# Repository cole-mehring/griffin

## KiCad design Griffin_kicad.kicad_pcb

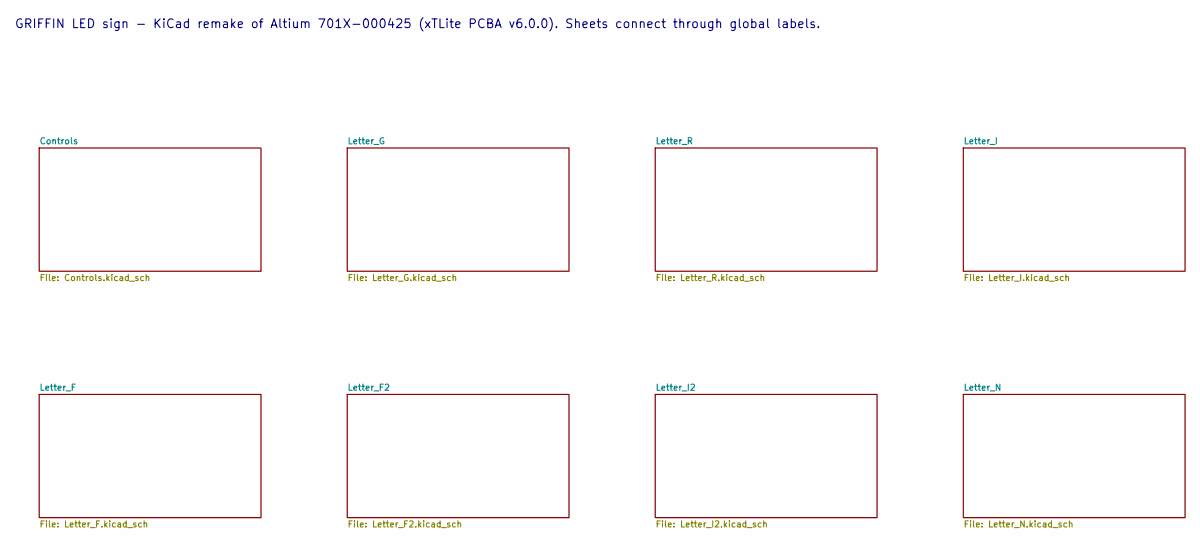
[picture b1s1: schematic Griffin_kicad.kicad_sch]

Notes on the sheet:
GRIFFIN LED sign - KiCad remake of Altium 701X-000425 (xTLite PCBA v6.0.0). Sheets connect through global labels.

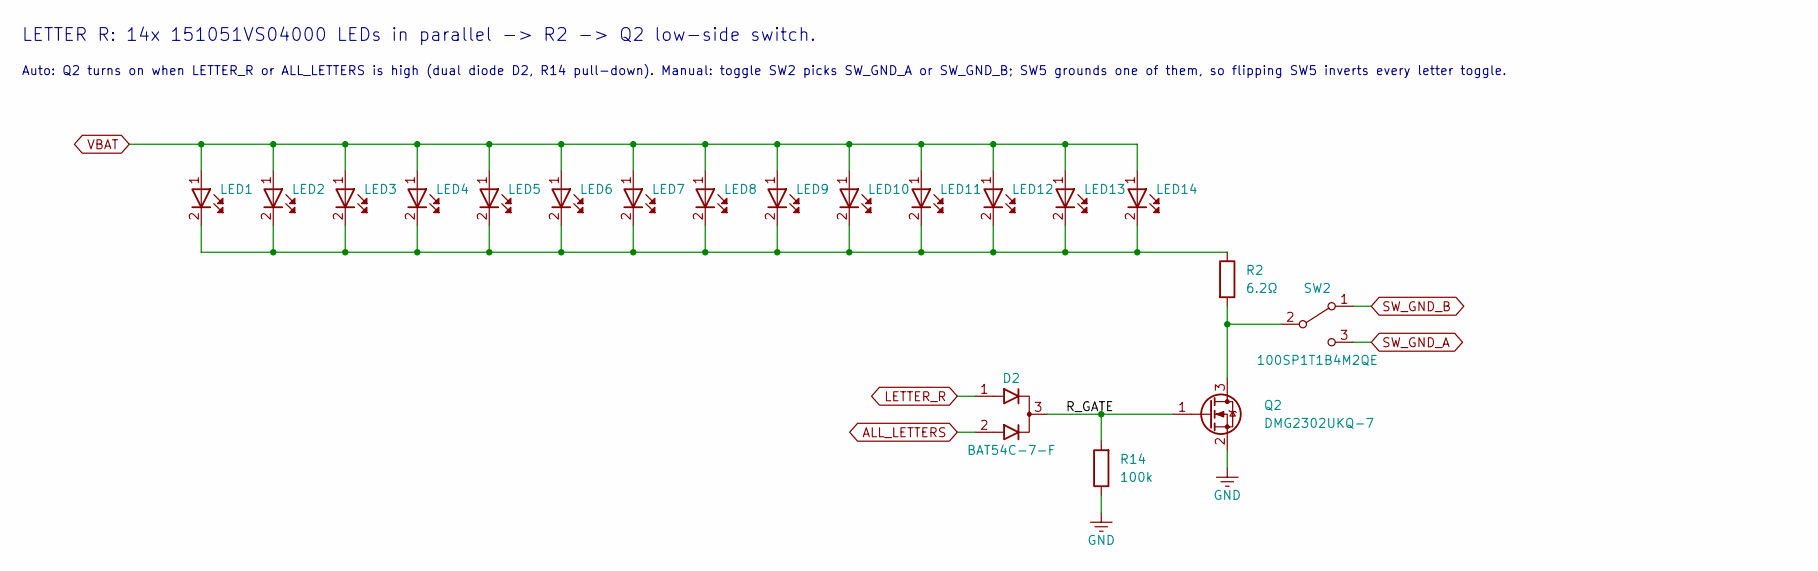
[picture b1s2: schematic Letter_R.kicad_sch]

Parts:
D2: BAT54C-7-F; SOT-23_Diodes; MPN BAT54C-7-F
LED1, LED2, LED3, LED4, LED5, LED6, LED7, LED8, LED9, LED10, LED11, LED12, LED13, LED14: 151051VS04000; LED_D5.0mm_WE-WL-TMRC_AnodePin1; MPN 151051VS04000
Q2: DMG2302UKQ-7; SOT-23_Diodes; MPN DMG2302UKQ-7
R2: 6.2Ω; R_1206_3216Metric; MPN RC1206FR-076R2L
R14: 100k; R_0805_2012Metric; MPN RC0805FR-07100KL
SW2: 100SP1T1B4M2QE; SW_Toggle_E-Switch_100SP_M2_P4.70mm; MPN 100SP1T1B4M2QE

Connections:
/Letter_R/R_GATE: D2.3 (K), Q2.1 (G), R14.2
ALL_LETTERS: D2.2 (A2); also elsewhere on the board
GND: Q2.2 (S), R14.1; also elsewhere on the board
LETTER_R: D2.1 (A1); also elsewhere on the board
unnamed: LED1.2 (K), LED2.2 (K), LED3.2 (K), LED4.2 (K), LED5.2 (K), LED6.2 (K), LED7.2 (K), LED8.2 (K), LED9.2 (K), LED10.2 (K), LED11.2 (K), LED12.2 (K), LED13.2 (K), LED14.2 (K), R2.1
unnamed: Q2.3 (D), R2.2, SW2.2 (C)
SW_GND_A: SW2.3 (B); also elsewhere on the board
SW_GND_B: SW2.1 (A); also elsewhere on the board
VBAT: LED1.1 (A), LED2.1 (A), LED3.1 (A), LED4.1 (A), LED5.1 (A), LED6.1 (A), LED7.1 (A), LED8.1 (A), LED9.1 (A), LED10.1 (A), LED11.1 (A), LED12.1 (A), LED13.1 (A), LED14.1 (A); also elsewhere on the board

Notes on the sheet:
Auto: Q2 turns on when LETTER_R or ALL_LETTERS is high (dual diode D2, R14 pull-down). Manual: toggle SW2 picks SW_GND_A or SW_GND_B; SW5 grounds one of them, so flipping SW5 inverts every letter toggle.
LETTER R: 14x 151051VS04000 LEDs in parallel -> R2 -> Q2 low-side switch.

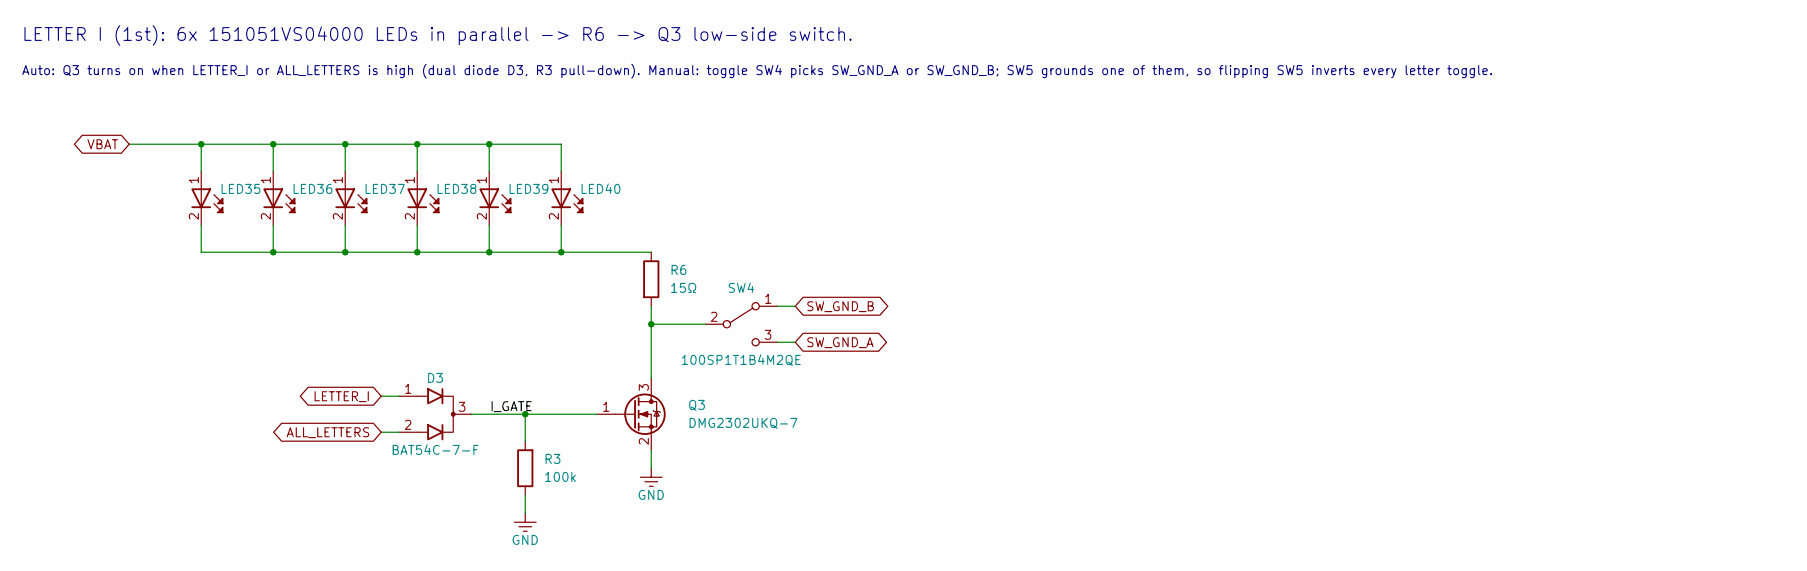
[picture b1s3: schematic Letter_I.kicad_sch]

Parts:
D3: BAT54C-7-F; SOT-23_Diodes; MPN BAT54C-7-F
LED35, LED36, LED37, LED38, LED39, LED40: 151051VS04000; LED_D5.0mm_WE-WL-TMRC_AnodePin1; MPN 151051VS04000
Q3: DMG2302UKQ-7; SOT-23_Diodes; MPN DMG2302UKQ-7
R3: 100k; R_0805_2012Metric; MPN RC0805FR-07100KL
R6: 15Ω; R_1206_3216Metric; MPN RC1206FR-0715RL
SW4: 100SP1T1B4M2QE; SW_Toggle_E-Switch_100SP_M2_P4.70mm; MPN 100SP1T1B4M2QE

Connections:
/Letter_I/I_GATE: D3.3 (K), Q3.1 (G), R3.2
ALL_LETTERS: D3.2 (A2); also elsewhere on the board
GND: Q3.2 (S), R3.1; also elsewhere on the board
LETTER_I: D3.1 (A1); also elsewhere on the board
unnamed: LED35.2 (K), LED36.2 (K), LED37.2 (K), LED38.2 (K), LED39.2 (K), LED40.2 (K), R6.1
unnamed: Q3.3 (D), R6.2, SW4.2 (C)
SW_GND_A: SW4.3 (B); also elsewhere on the board
SW_GND_B: SW4.1 (A); also elsewhere on the board
VBAT: LED35.1 (A), LED36.1 (A), LED37.1 (A), LED38.1 (A), LED39.1 (A), LED40.1 (A); also elsewhere on the board

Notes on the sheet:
Auto: Q3 turns on when LETTER_I or ALL_LETTERS is high (dual diode D3, R3 pull-down). Manual: toggle SW4 picks SW_GND_A or SW_GND_B; SW5 grounds one of them, so flipping SW5 inverts every letter toggle.
LETTER I (1st): 6x 151051VS04000 LEDs in parallel -> R6 -> Q3 low-side switch.

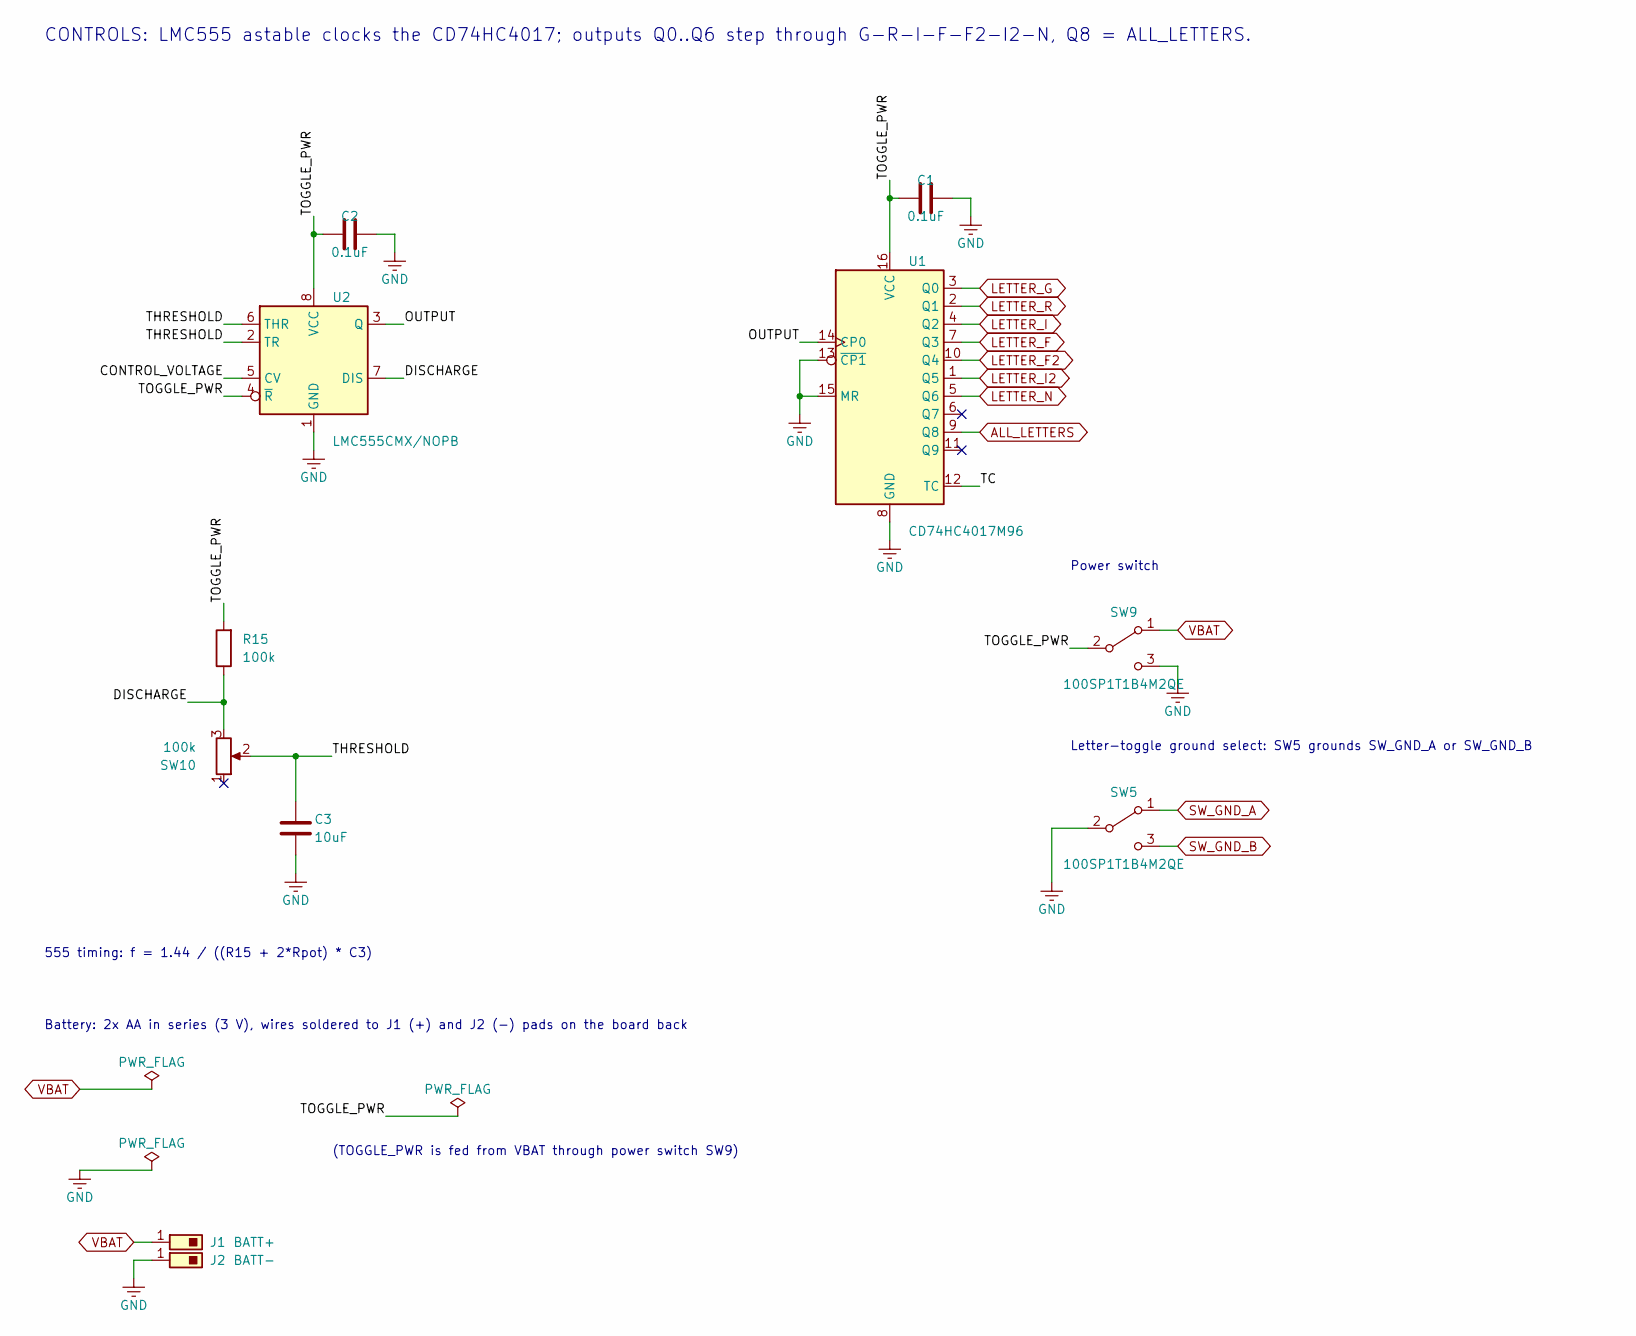
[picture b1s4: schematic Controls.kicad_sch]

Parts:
C1, C2: 0.1uF; C_0805_2012Metric; MPN CC0805KRX7R9BB104
C3: 10uF; C_0805_2012Metric; MPN GRM21BR61E106KA73L
J1: BATT+; SolderPad_1x1_8x8mm
J2: BATT-; SolderPad_1x1_8x8mm
R15: 100k; R_0805_2012Metric; MPN RC0805FR-07100KL
SW5, SW9: 100SP1T1B4M2QE; SW_Toggle_E-Switch_100SP_M2_P4.70mm; MPN 100SP1T1B4M2QE
SW10: 100k; Potentiometer_Bourns_PTV09A-4_Single_Vertical; MPN PTV09A-4025F-B104
U1: CD74HC4017M96; SOIC-16_3.9x9.9mm_P1.27mm; MPN CD74HC4017M96
U2: LMC555CMX/NOPB; SOIC-8_3.9x4.9mm_P1.27mm; MPN LMC555CMX/NOPB

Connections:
/Controls/CONTROL_VOLTAGE: U2.5 (CV)
/Controls/DISCHARGE: R15.1, SW10.3, U2.7 (DIS)
/Controls/OUTPUT: U1.14 (CP0), U2.3 (Q)
/Controls/TC: U1.12 (TC)
/Controls/THRESHOLD: C3.1, SW10.2, U2.2 (TR), U2.6 (THR)
/Controls/TOGGLE_PWR: C1.1, C2.1, R15.2, SW9.2 (C), U1.16 (VCC), U2.4 (~R), U2.8 (VCC)
ALL_LETTERS: U1.9 (Q8); also elsewhere on the board
GND: C1.2, C2.2, C3.2, J2.1 (~_1), SW5.2 (C), SW9.3 (B), U1.8 (GND), U1.13 (~CP1), U1.15 (MR), U2.1 (GND); also elsewhere on the board
LETTER_F: U1.7 (Q3); also elsewhere on the board
LETTER_F2: U1.10 (Q4); also elsewhere on the board
LETTER_G: U1.3 (Q0); also elsewhere on the board
LETTER_I: U1.4 (Q2); also elsewhere on the board
LETTER_I2: U1.1 (Q5); also elsewhere on the board
LETTER_N: U1.5 (Q6); also elsewhere on the board
LETTER_R: U1.2 (Q1); also elsewhere on the board
SW_GND_A: SW5.1 (A); also elsewhere on the board
SW_GND_B: SW5.3 (B); also elsewhere on the board
VBAT: J1.1 (~_1), SW9.1 (A); also elsewhere on the board

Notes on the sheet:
(TOGGLE_PWR is fed from VBAT through power switch SW9)
Battery: 2x AA in series (3 V), wires soldered to J1 (+) and J2 (-) pads on the board back
Letter-toggle ground select: SW5 grounds SW_GND_A or SW_GND_B
555 timing: f = 1.44 / ((R15 + 2*Rpot) * C3)
CONTROLS: LMC555 astable clocks the CD74HC4017; outputs Q0..Q6 step through G-R-I-F-F2-I2-N, Q8 = ALL_LETTERS.
Power switch

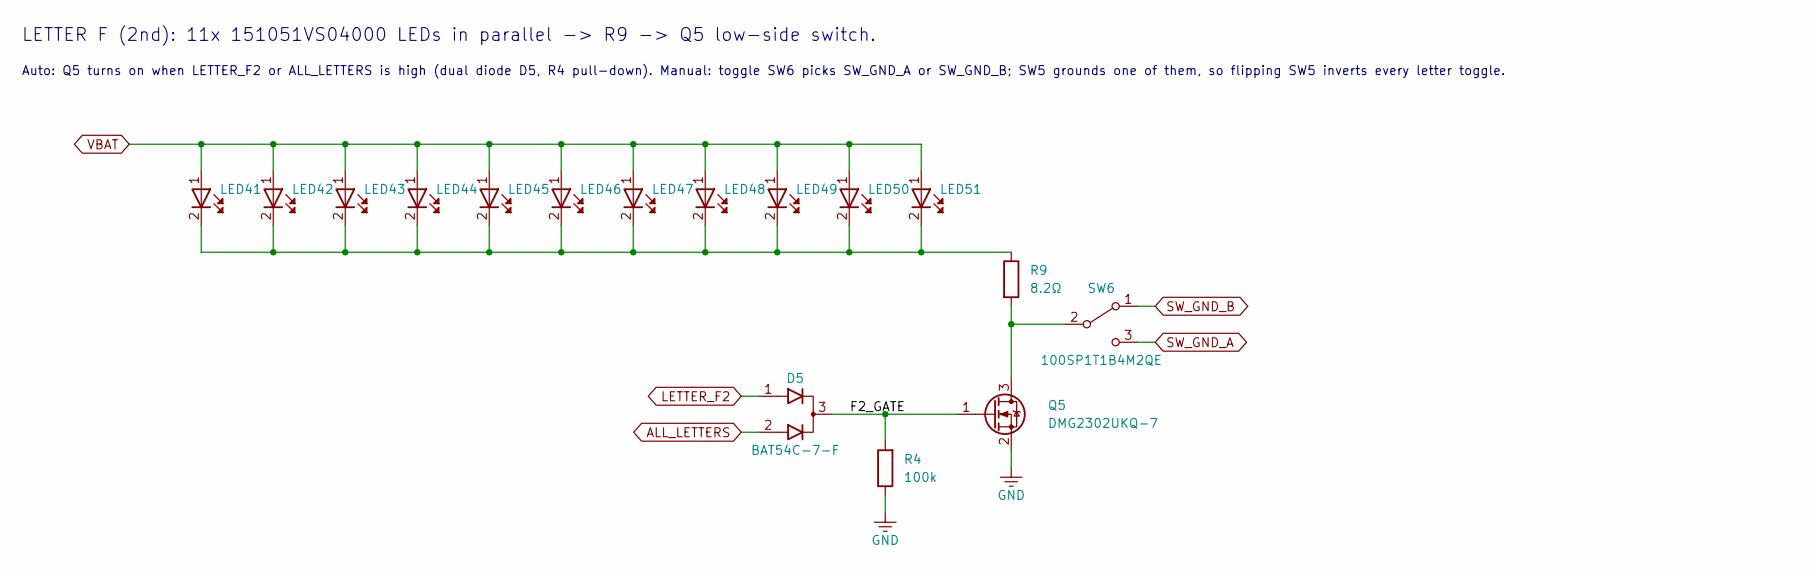
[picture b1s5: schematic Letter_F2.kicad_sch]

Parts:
D5: BAT54C-7-F; SOT-23_Diodes; MPN BAT54C-7-F
LED41, LED42, LED43, LED44, LED45, LED46, LED47, LED48, LED49, LED50, LED51: 151051VS04000; LED_D5.0mm_WE-WL-TMRC_AnodePin1; MPN 151051VS04000
Q5: DMG2302UKQ-7; SOT-23_Diodes; MPN DMG2302UKQ-7
R4: 100k; R_0805_2012Metric; MPN RC0805FR-07100KL
R9: 8.2Ω; R_1206_3216Metric; MPN RC1206FR-078R2L
SW6: 100SP1T1B4M2QE; SW_Toggle_E-Switch_100SP_M2_P4.70mm; MPN 100SP1T1B4M2QE

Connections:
/Letter_F2/F2_GATE: D5.3 (K), Q5.1 (G), R4.2
ALL_LETTERS: D5.2 (A2); also elsewhere on the board
GND: Q5.2 (S), R4.1; also elsewhere on the board
LETTER_F2: D5.1 (A1); also elsewhere on the board
unnamed: LED41.2 (K), LED42.2 (K), LED43.2 (K), LED44.2 (K), LED45.2 (K), LED46.2 (K), LED47.2 (K), LED48.2 (K), LED49.2 (K), LED50.2 (K), LED51.2 (K), R9.1
unnamed: Q5.3 (D), R9.2, SW6.2 (C)
SW_GND_A: SW6.3 (B); also elsewhere on the board
SW_GND_B: SW6.1 (A); also elsewhere on the board
VBAT: LED41.1 (A), LED42.1 (A), LED43.1 (A), LED44.1 (A), LED45.1 (A), LED46.1 (A), LED47.1 (A), LED48.1 (A), LED49.1 (A), LED50.1 (A), LED51.1 (A); also elsewhere on the board

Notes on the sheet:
Auto: Q5 turns on when LETTER_F2 or ALL_LETTERS is high (dual diode D5, R4 pull-down). Manual: toggle SW6 picks SW_GND_A or SW_GND_B; SW5 grounds one of them, so flipping SW5 inverts every letter toggle.
LETTER F (2nd): 11x 151051VS04000 LEDs in parallel -> R9 -> Q5 low-side switch.

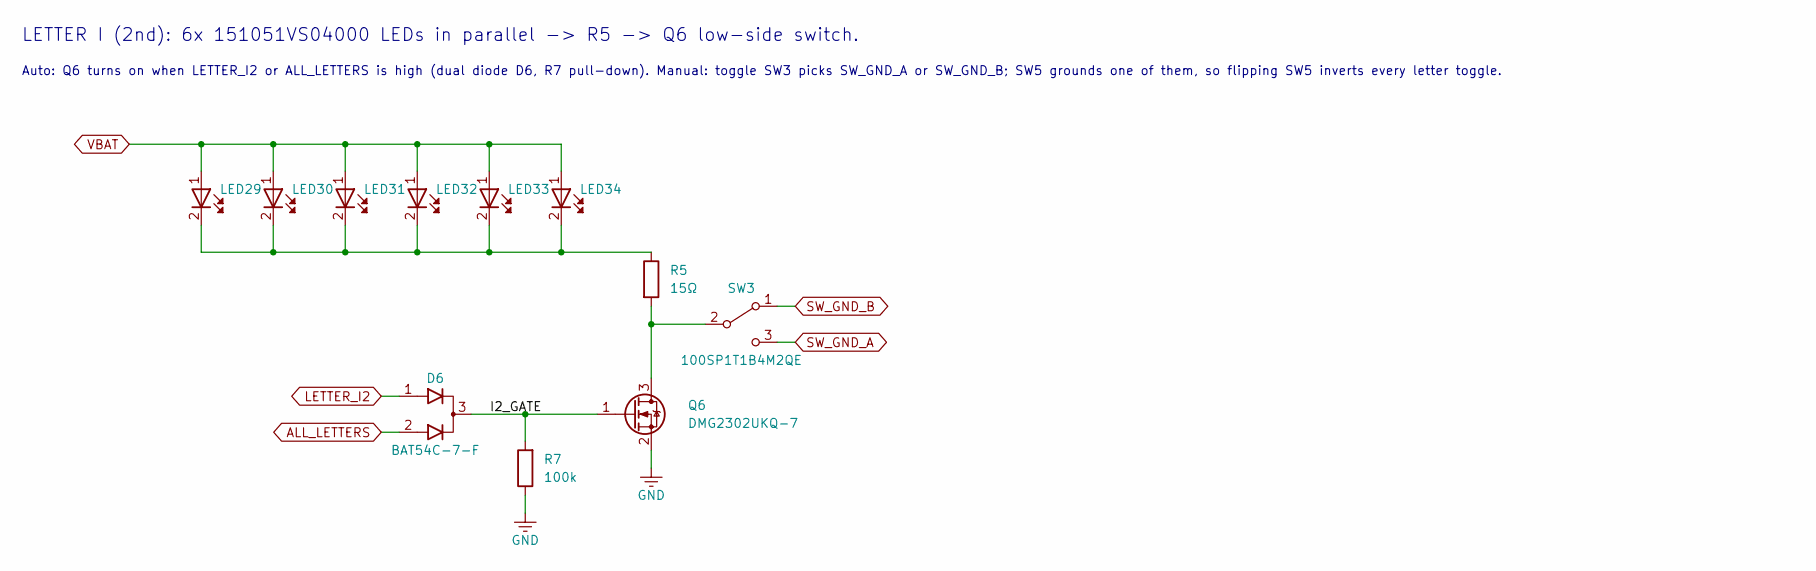
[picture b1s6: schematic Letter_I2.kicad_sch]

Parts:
D6: BAT54C-7-F; SOT-23_Diodes; MPN BAT54C-7-F
LED29, LED30, LED31, LED32, LED33, LED34: 151051VS04000; LED_D5.0mm_WE-WL-TMRC_AnodePin1; MPN 151051VS04000
Q6: DMG2302UKQ-7; SOT-23_Diodes; MPN DMG2302UKQ-7
R5: 15Ω; R_1206_3216Metric; MPN RC1206FR-0715RL
R7: 100k; R_0805_2012Metric; MPN RC0805FR-07100KL
SW3: 100SP1T1B4M2QE; SW_Toggle_E-Switch_100SP_M2_P4.70mm; MPN 100SP1T1B4M2QE

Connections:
/Letter_I2/I2_GATE: D6.3 (K), Q6.1 (G), R7.2
ALL_LETTERS: D6.2 (A2); also elsewhere on the board
GND: Q6.2 (S), R7.1; also elsewhere on the board
LETTER_I2: D6.1 (A1); also elsewhere on the board
unnamed: LED29.2 (K), LED30.2 (K), LED31.2 (K), LED32.2 (K), LED33.2 (K), LED34.2 (K), R5.1
unnamed: Q6.3 (D), R5.2, SW3.2 (C)
SW_GND_A: SW3.3 (B); also elsewhere on the board
SW_GND_B: SW3.1 (A); also elsewhere on the board
VBAT: LED29.1 (A), LED30.1 (A), LED31.1 (A), LED32.1 (A), LED33.1 (A), LED34.1 (A); also elsewhere on the board

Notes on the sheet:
LETTER I (2nd): 6x 151051VS04000 LEDs in parallel -> R5 -> Q6 low-side switch.
Auto: Q6 turns on when LETTER_I2 or ALL_LETTERS is high (dual diode D6, R7 pull-down). Manual: toggle SW3 picks SW_GND_A or SW_GND_B; SW5 grounds one of them, so flipping SW5 inverts every letter toggle.

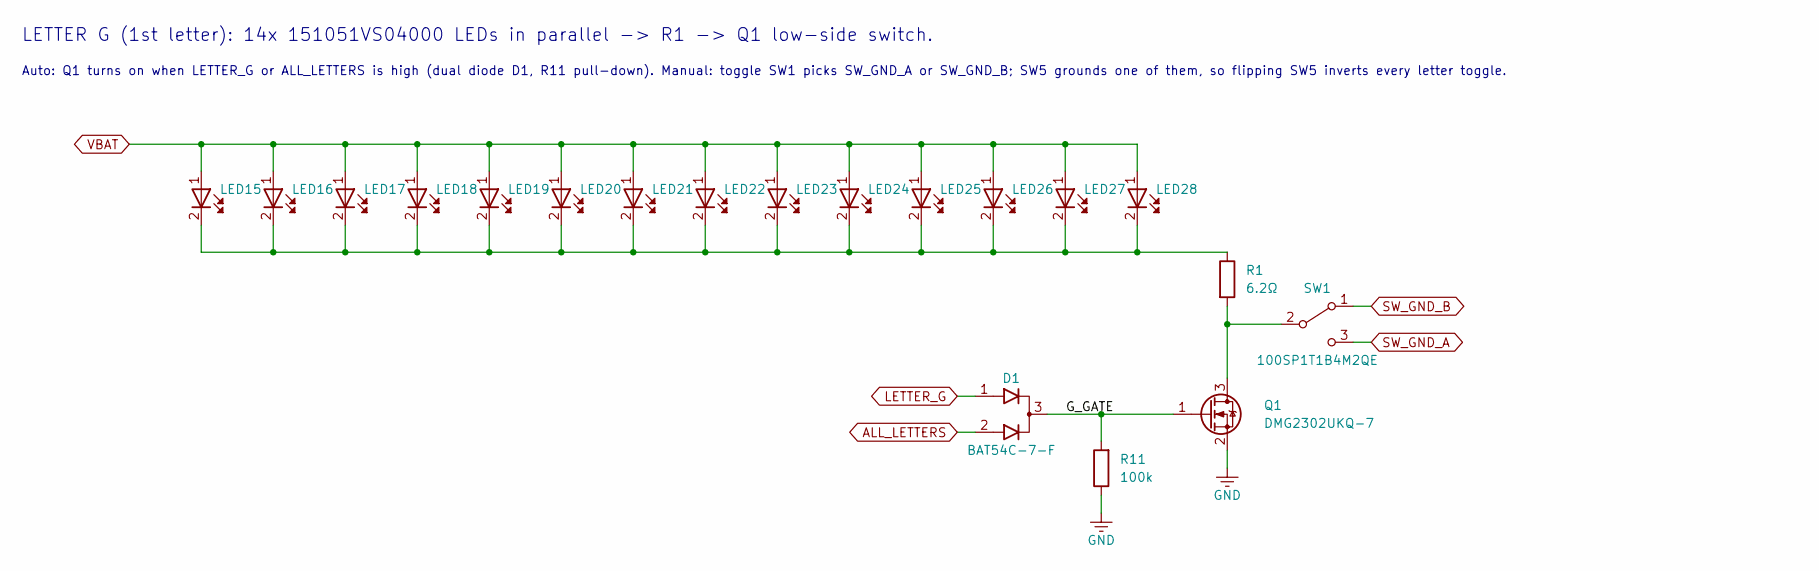
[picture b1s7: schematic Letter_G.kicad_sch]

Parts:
D1: BAT54C-7-F; SOT-23_Diodes; MPN BAT54C-7-F
LED15, LED16, LED17, LED18, LED19, LED20, LED21, LED22, LED23, LED24, LED25, LED26, LED27, LED28: 151051VS04000; LED_D5.0mm_WE-WL-TMRC_AnodePin1; MPN 151051VS04000
Q1: DMG2302UKQ-7; SOT-23_Diodes; MPN DMG2302UKQ-7
R1: 6.2Ω; R_1206_3216Metric; MPN RC1206FR-076R2L
R11: 100k; R_0805_2012Metric; MPN RC0805FR-07100KL
SW1: 100SP1T1B4M2QE; SW_Toggle_E-Switch_100SP_M2_P4.70mm; MPN 100SP1T1B4M2QE

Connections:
/Letter_G/G_GATE: D1.3 (K), Q1.1 (G), R11.2
ALL_LETTERS: D1.2 (A2); also elsewhere on the board
GND: Q1.2 (S), R11.1; also elsewhere on the board
LETTER_G: D1.1 (A1); also elsewhere on the board
unnamed: LED15.2 (K), LED16.2 (K), LED17.2 (K), LED18.2 (K), LED19.2 (K), LED20.2 (K), LED21.2 (K), LED22.2 (K), LED23.2 (K), LED24.2 (K), LED25.2 (K), LED26.2 (K), LED27.2 (K), LED28.2 (K), R1.1
unnamed: Q1.3 (D), R1.2, SW1.2 (C)
SW_GND_A: SW1.3 (B); also elsewhere on the board
SW_GND_B: SW1.1 (A); also elsewhere on the board
VBAT: LED15.1 (A), LED16.1 (A), LED17.1 (A), LED18.1 (A), LED19.1 (A), LED20.1 (A), LED21.1 (A), LED22.1 (A), LED23.1 (A), LED24.1 (A), LED25.1 (A), LED26.1 (A), LED27.1 (A), LED28.1 (A); also elsewhere on the board

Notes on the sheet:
Auto: Q1 turns on when LETTER_G or ALL_LETTERS is high (dual diode D1, R11 pull-down). Manual: toggle SW1 picks SW_GND_A or SW_GND_B; SW5 grounds one of them, so flipping SW5 inverts every letter toggle.
LETTER G (1st letter): 14x 151051VS04000 LEDs in parallel -> R1 -> Q1 low-side switch.

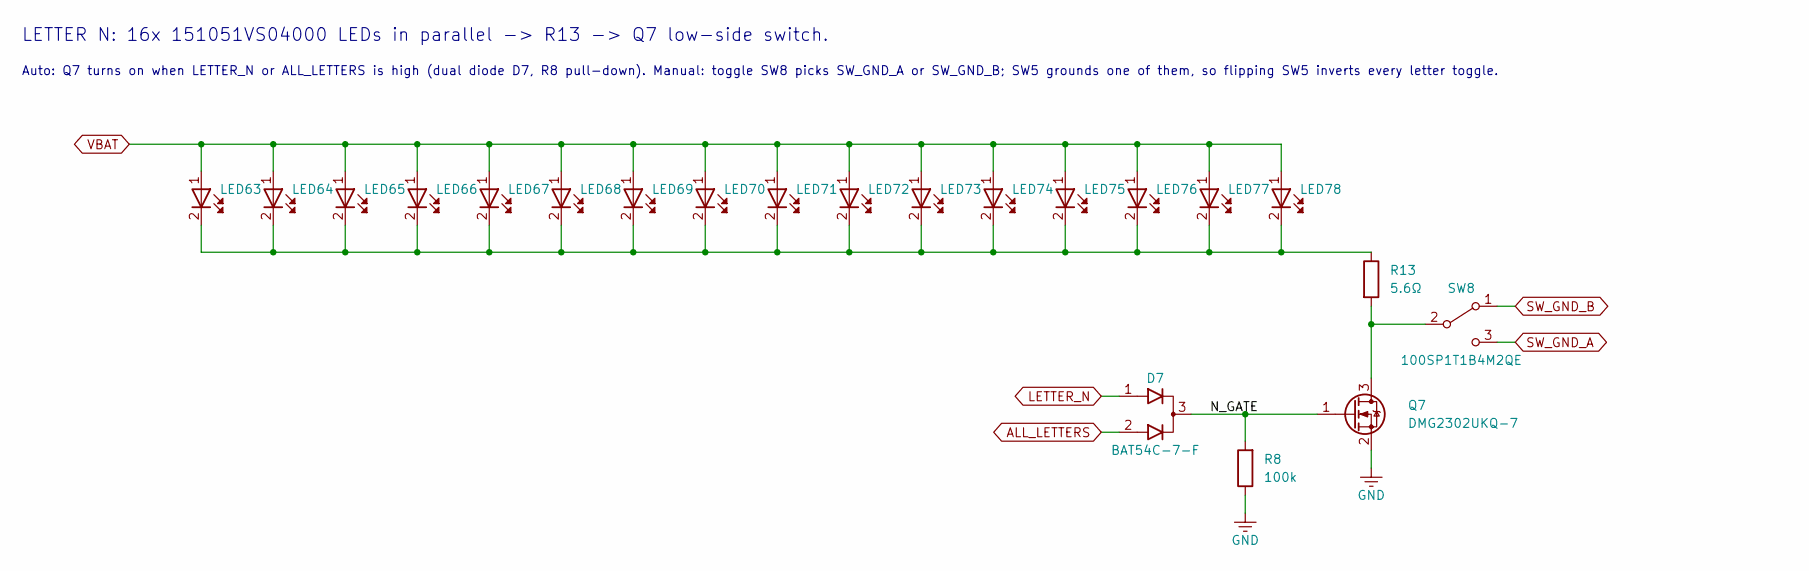
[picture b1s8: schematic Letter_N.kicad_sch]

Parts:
D7: BAT54C-7-F; SOT-23_Diodes; MPN BAT54C-7-F
LED63, LED64, LED65, LED66, LED67, LED68, LED69, LED70, LED71, LED72, LED73, LED74, LED75, LED76, LED77, LED78: 151051VS04000; LED_D5.0mm_WE-WL-TMRC_AnodePin1; MPN 151051VS04000
Q7: DMG2302UKQ-7; SOT-23_Diodes; MPN DMG2302UKQ-7
R8: 100k; R_0805_2012Metric; MPN RC0805FR-07100KL
R13: 5.6Ω; R_1206_3216Metric; MPN RC1206FR-075R6L
SW8: 100SP1T1B4M2QE; SW_Toggle_E-Switch_100SP_M2_P4.70mm; MPN 100SP1T1B4M2QE

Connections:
/Letter_N/N_GATE: D7.3 (K), Q7.1 (G), R8.2
ALL_LETTERS: D7.2 (A2); also elsewhere on the board
GND: Q7.2 (S), R8.1; also elsewhere on the board
LETTER_N: D7.1 (A1); also elsewhere on the board
unnamed: LED63.2 (K), LED64.2 (K), LED65.2 (K), LED66.2 (K), LED67.2 (K), LED68.2 (K), LED69.2 (K), LED70.2 (K), LED71.2 (K), LED72.2 (K), LED73.2 (K), LED74.2 (K), LED75.2 (K), LED76.2 (K), LED77.2 (K), LED78.2 (K), R13.1
unnamed: Q7.3 (D), R13.2, SW8.2 (C)
SW_GND_A: SW8.3 (B); also elsewhere on the board
SW_GND_B: SW8.1 (A); also elsewhere on the board
VBAT: LED63.1 (A), LED64.1 (A), LED65.1 (A), LED66.1 (A), LED67.1 (A), LED68.1 (A), LED69.1 (A), LED70.1 (A), LED71.1 (A), LED72.1 (A), LED73.1 (A), LED74.1 (A), LED75.1 (A), LED76.1 (A), LED77.1 (A), LED78.1 (A); also elsewhere on the board

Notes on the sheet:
LETTER N: 16x 151051VS04000 LEDs in parallel -> R13 -> Q7 low-side switch.
Auto: Q7 turns on when LETTER_N or ALL_LETTERS is high (dual diode D7, R8 pull-down). Manual: toggle SW8 picks SW_GND_A or SW_GND_B; SW5 grounds one of them, so flipping SW5 inverts every letter toggle.

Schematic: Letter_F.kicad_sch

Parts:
D4: BAT54C-7-F; SOT-23_Diodes; MPN BAT54C-7-F
LED52, LED53, LED54, LED55, LED56, LED57, LED58, LED59, LED60, LED61, LED62: 151051VS04000; LED_D5.0mm_WE-WL-TMRC_AnodePin1; MPN 151051VS04000
Q4: DMG2302UKQ-7; SOT-23_Diodes; MPN DMG2302UKQ-7
R10: 8.2Ω; R_1206_3216Metric; MPN RC1206FR-078R2L
R12: 100k; R_0805_2012Metric; MPN RC0805FR-07100KL
SW7: 100SP1T1B4M2QE; SW_Toggle_E-Switch_100SP_M2_P4.70mm; MPN 100SP1T1B4M2QE

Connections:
/Letter_F/F_GATE: D4.3 (K), Q4.1 (G), R12.2
ALL_LETTERS: D4.2 (A2); also elsewhere on the board
GND: Q4.2 (S), R12.1; also elsewhere on the board
LETTER_F: D4.1 (A1); also elsewhere on the board
unnamed: LED52.2 (K), LED53.2 (K), LED54.2 (K), LED55.2 (K), LED56.2 (K), LED57.2 (K), LED58.2 (K), LED59.2 (K), LED60.2 (K), LED61.2 (K), LED62.2 (K), R10.1
unnamed: Q4.3 (D), R10.2, SW7.2 (C)
SW_GND_A: SW7.3 (B); also elsewhere on the board
SW_GND_B: SW7.1 (A); also elsewhere on the board
VBAT: LED52.1 (A), LED53.1 (A), LED54.1 (A), LED55.1 (A), LED56.1 (A), LED57.1 (A), LED58.1 (A), LED59.1 (A), LED60.1 (A), LED61.1 (A), LED62.1 (A); also elsewhere on the board

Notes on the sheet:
LETTER F (1st): 11x 151051VS04000 LEDs in parallel -> R10 -> Q4 low-side switch.
Auto: Q4 turns on when LETTER_F or ALL_LETTERS is high (dual diode D4, R12 pull-down). Manual: toggle SW7 picks SW_GND_A or SW_GND_B; SW5 grounds one of them, so flipping SW5 inverts every letter toggle.

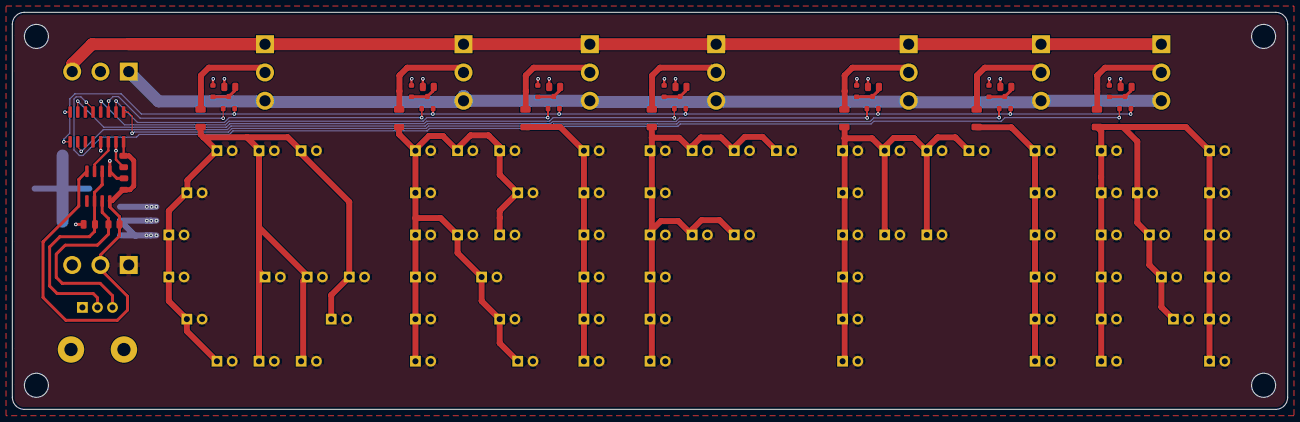
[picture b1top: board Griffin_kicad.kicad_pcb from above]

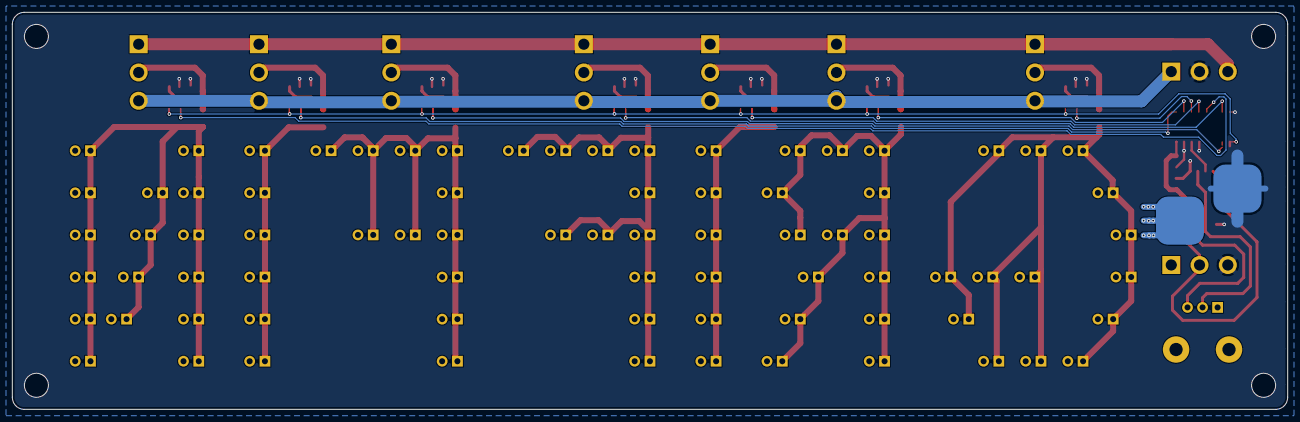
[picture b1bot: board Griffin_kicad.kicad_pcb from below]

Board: 2 copper layers, 212.0 x 66.0 mm, 128 parts (2 on the bottom side), 37 nets.

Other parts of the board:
H1, H2, H3, H4: MountingHole_4.0mm; MountingHole_4.0mm_NPTH
